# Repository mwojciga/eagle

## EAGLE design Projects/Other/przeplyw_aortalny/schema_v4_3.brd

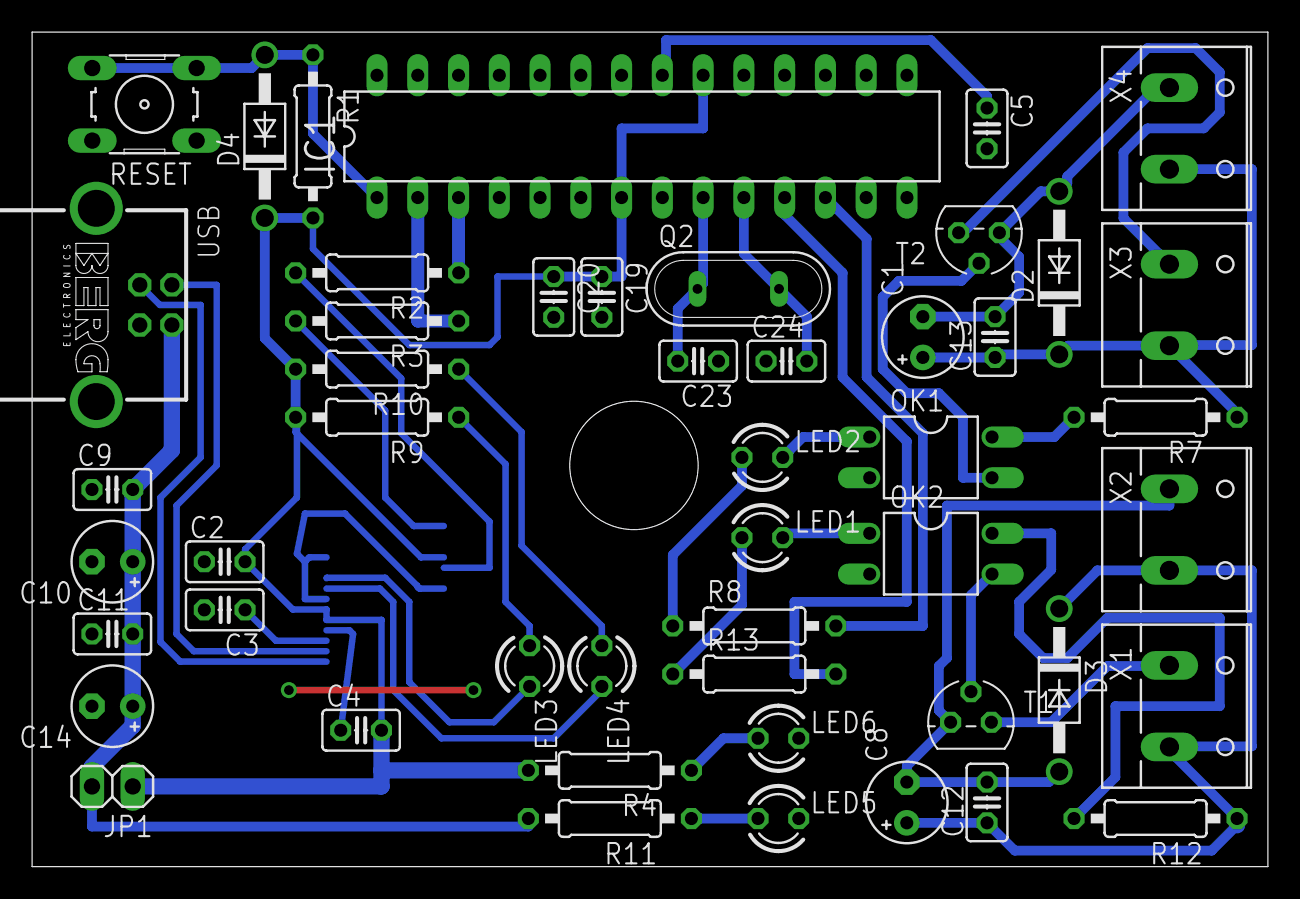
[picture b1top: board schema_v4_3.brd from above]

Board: 2 copper layers, 77.0 x 52.0 mm, 50 parts (1 on the bottom side), 36 nets.

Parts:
C1, C8, C10: 1uF; E2,5-5
C2, C3, C4, C5, C9, C11, C12, C13, C19, C20: 100nF; C025-025X050
C14: 4,7uF; E2,5-5
C23, C24: 22pF; C025-025X050
D2, D3, D4: 1N4001; DO41-10
FT232RL: FT232RL; SSOP28DB
IC1: MEGA8-P; DIL28-3
JP1: 1X02
LED1, LED2, LED3, LED4, LED5, LED6: LED3MM
OK1, OK2: LTV816; DIL04
Q2: QS
R1: 22k; 0207/10
R2, R3: 1k; 0207/10
R4, R8, R9, R10, R11, R13: 330; 0207/10
R7, R12: 10k; 0207/10
RESET: B3F-10XX
T1, T2: BC547; TO92
USB: PN61729-S
X1, X2, X3, X4: W237-132

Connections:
5V0: C2.2, C4.2, C19.1, C20.1, D4.C, FT232RL.4, FT232RL.19, FT232RL.20, IC1.7, IC1.20, JP1.1, R1.2, R4.2, R9.2, R10.2
5V0_USB: C9.2, C10.+, C11.2, C14.+, JP1.2, R11.2, USB.1
GND: C2.1, C3.2, C4.1, C5.2, C9.1, C10.-, C11.1, C14.-, C19.2, C20.2, C23.1, C24.1, FT232RL.7, FT232RL.18, FT232RL.21, FT232RL.25, FT232RL.26, IC1.8, IC1.22, LED5.K, LED6.K, OK1.2, OK2.2, RESET.1, RESET.2, USB.4, USB.S1, USB.S2
MOTOR1: IC1.11, R13.2
MOTOR2: IC1.12, R8.2
unnamed: IC1.3, R2.1
unnamed: IC1.2, R3.1
unnamed: LED6.A, R4.1
unnamed: LED1.A, R13.1
unnamed: LED1.K, OK2.1
unnamed: LED2.A, R8.1
unnamed: LED3.A, R9.1
unnamed: LED4.A, R10.1
unnamed: LED5.A, R11.1
unnamed: C1.+, C13.1, D2.C, R7.1, X3.2, X4.2
unnamed: LED2.K, OK1.1
unnamed: C1.-, C13.2, D2.A, T2.3, X4.1
unnamed: OK1.3, T2.2
unnamed: OK2.4, R12.2
unnamed: T1.1, X1.1
unnamed: C8.+, C12.1, D3.C, R12.1, X1.2, X2.2
unnamed: C8.-, C12.2, D3.A, T1.3, X2.1
unnamed: OK2.3, T1.2
unnamed: C5.1, IC1.21
unnamed: C23.2, IC1.9, Q2.1
unnamed: C24.2, IC1.10, Q2.2
unnamed: FT232RL.23, LED3.K
unnamed: FT232RL.22, LED4.K
unnamed: C3.1, FT232RL.17
unnamed: OK1.4, R7.2
unnamed: T2.1, X3.1
RESET: D4.A, IC1.1, R1.1, RESET.3, RESET.4
RXD: FT232RL.1, R3.2
TXD: FT232RL.5, R2.2
USBDM: FT232RL.16, USB.2
USBDP: FT232RL.15, USB.3
